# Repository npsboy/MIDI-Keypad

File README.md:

# MIDI Keypad — 8-bit edition

- **Sliders removed.** The encoder and the 3 Choc switches now share one top row, which frees a band above the keys.
- **A 5mm addressable RGB LED above each of the 7 touch keys.** They chain after the tutorial's 3 NeoPixels, so they use **no extra pins**.
- **A passive buzzer** (5V, 2048 Hz, 8 mm pin spacing), driven by a BC547 with a flyback diode.
- **Retro / chiptune pixel-art silkscreen** on both sides.

The finished project is in this folder (`MIDI-Keypad.kicad_pro`). Final checks: **ERC 0 errors / 0 warnings, DRC 0 violations / 0 unconnected** (`ERC_report.txt`, `DRC_report.txt`). Files to order with are in `production/`.

## Folder layout
- `MIDI-Keypad.*`: the finished KiCad project
- `production/`: Gerber zip for JLCPCB, BOM, positions, netlist
- `libraries/`: everything the project needs, linked relative to the project (no global KiCad setup required):
  - the tutorial's Hack Club symbols and footprints
  - this project's own symbol and footprints (`MIDI-Keypad.*`)
  - the 3D models

## Pin map (for the firmware)
| ESP32-S3-Zero pin | Function |
|---|---|
| GP2 | LED data: all 10 addressable LEDs, one chain |
| GP3 | Buzzer (PWM / tone). HIGH turns the transistor on |
| GP4 / GP5 / GP6 | SW3 / SW2 / SW1 (to GND, use internal pull-ups) |
| GP7 ... GP13 | TOUCH7 ... TOUCH1 (key 7 ... key 1, left to right is key 1 to 7) |
| TX (GPIO43) / RX (GPIO44) | Encoder A / B (to GND, use internal pull-ups) |
| GP1 | spare |

**LED chain order:**

| Index | LED | Position |
|---|---|---|
| 0 | D1 | under SW3 |
| 1 | D2 | under SW2 |
| 2 | D3 | under SW1 |
| 3-9 | D4-D10 | above keys 1-7 |

## Parts
| Ref | Qty | Part | Notes |
|---|---|---|---|
| U1 | 1 | Waveshare ESP32-S3-Zero | |
| SW1-SW3 | 3 | Kailh Choc low-profile switch | + Choc keycaps |
| SW4 | 1 | EC11 rotary encoder (vertical) | + a knob |
| D1-D3 | 3 | SK6812MINI-E | reverse-mounted on the back, shine through the board |
| D4-D10 | 7 | XINGLIGHT XL-504RGBC-WS2812B, 5mm | the Amazon.in listing B0HN43Y547. Pin 1 (DIN) is at the **flat side** |
| BZ1 | 1 | passive buzzer 5V 30mA 2048 Hz, 8 mm pitch | the Amazon.in listing B07M6517H8. "+" pin goes to the square pad |
| Q1 | 1 | BC547 (TO-92) | match the flat face to the flat side of the silkscreen outline. Collector goes on the square pad |
| R1 | 1 | 1 kΩ 1/4 W resistor | mounted standing up |
| D11 | 1 | 1N4148 | mounted standing up, **cathode (band) to the square pad** |

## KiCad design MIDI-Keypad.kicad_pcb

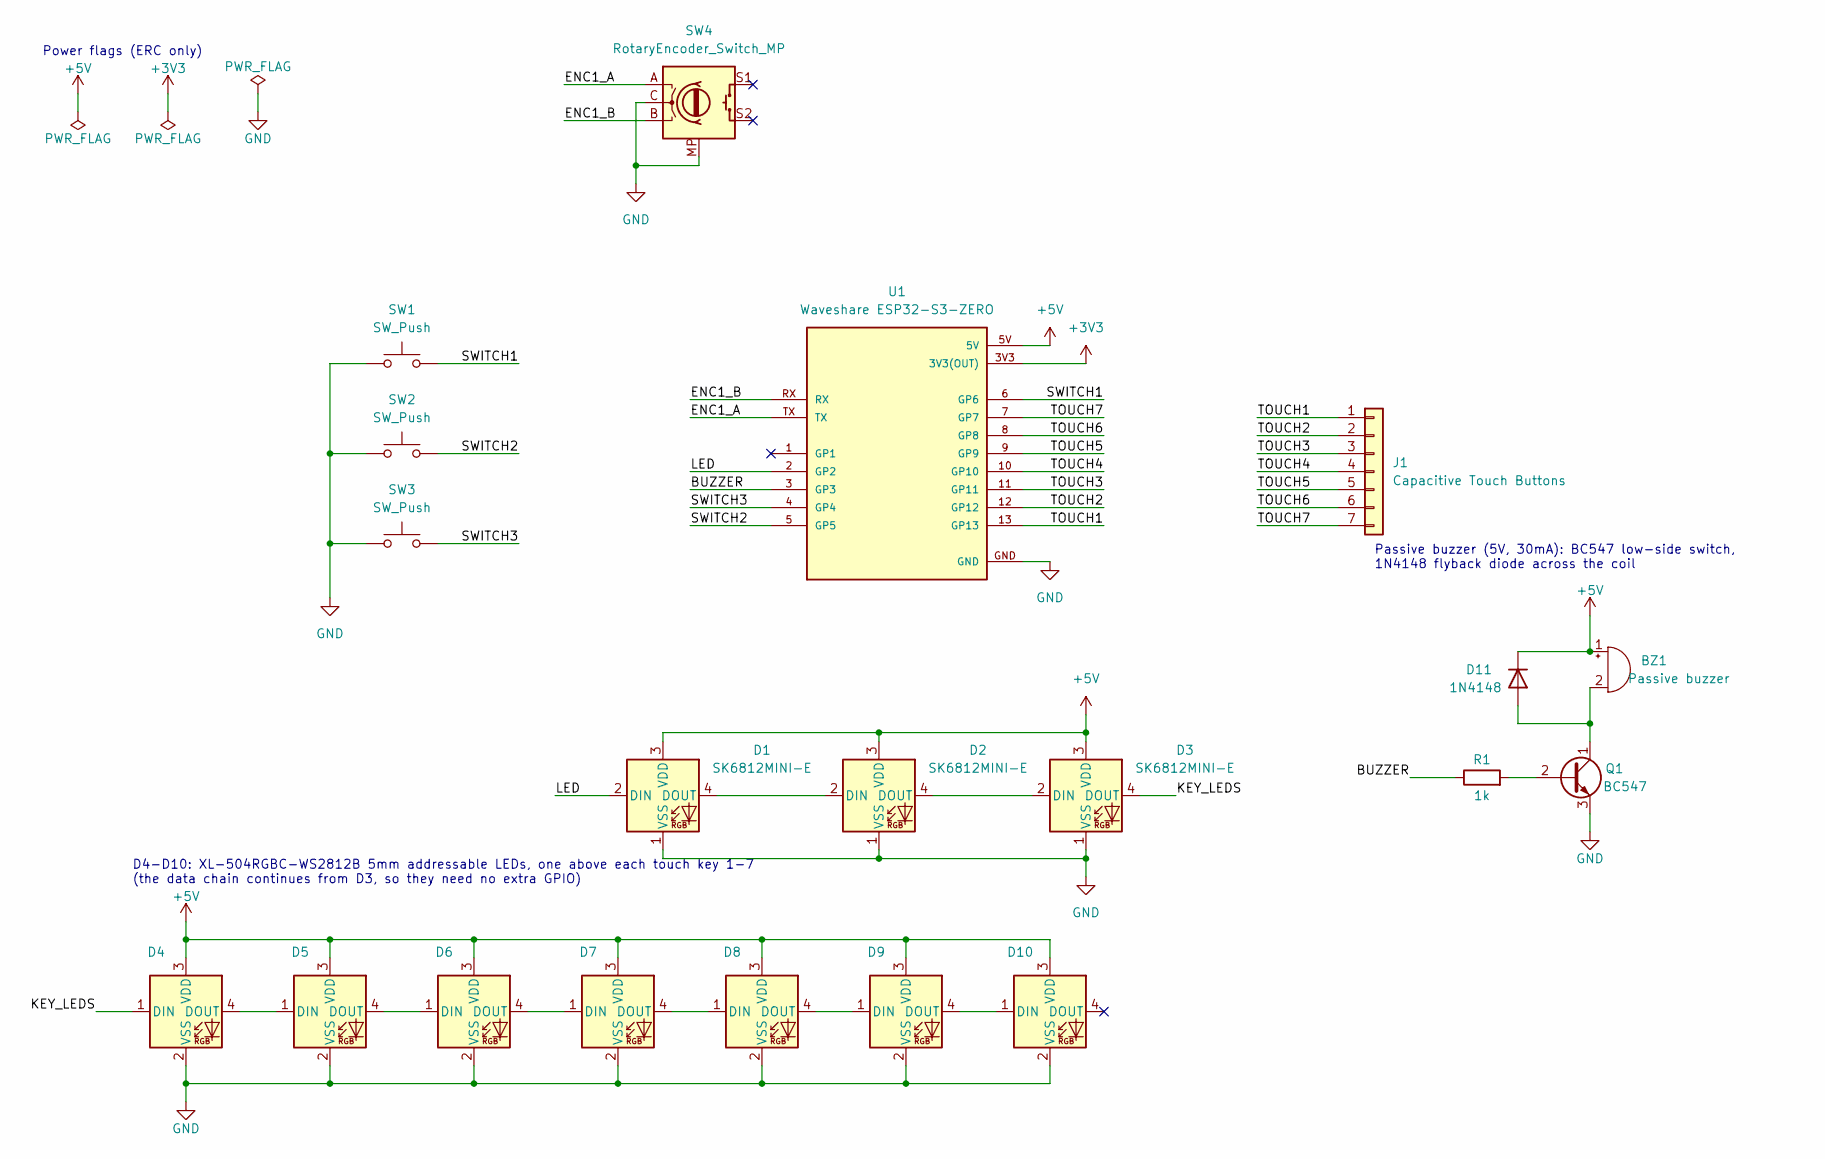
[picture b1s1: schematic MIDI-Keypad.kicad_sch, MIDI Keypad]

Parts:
BZ1: Passive buzzer; Buzzer_12x9.5_P8.0mm
D1, D2, D3: SK6812MINI-E; LED_SK6812MINI-E_3.2x2.8mm_P1.5mm_ReverseMount
D4, D5, D6, D7, D8, D9, D10: XL-504RGBC-WS2812B; LED_D5.0mm-4_XL-504RGBC-WS2812B
D11: 1N4148; D_DO-35_SOD27_P2.54mm_Vertical_CathodeUp
J1: Capacitive Touch Buttons; Capacitive Keys
Q1: BC547; TO-92_Inline
R1: 1k; R_Axial_DIN0207_L6.3mm_D2.5mm_P2.54mm_Vertical
SW1, SW2, SW3: SW_Push; Kailh Choc Low-Profile Switches
SW4: RotaryEncoder_Switch_MP; RotaryEncoder_Alps_EC11E-Switch_Vertical_H20mm
U1: Waveshare ESP32-S3-ZERO; Waveshare ESP32-S3-Zero; PARTREV NA

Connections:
+3V3: U1.3V3 (3V3(OUT))
+5V: BZ1.1 (+), D1.3 (VDD), D2.3 (VDD), D3.3 (VDD), D4.3 (VDD), D5.3 (VDD), D6.3 (VDD), D7.3 (VDD), D8.3 (VDD), D9.3 (VDD), D10.3 (VDD), D11.1 (K), U1.5V
/BUZZER: R1.1, U1.3 (GP3)
/ENC1_A: SW4.A, U1.TX
/ENC1_B: SW4.B, U1.RX
/KEY_LEDS: D3.4 (DOUT), D4.1 (DIN)
/LED: D1.2 (DIN), U1.2 (GP2)
/SWITCH1: SW1.2, U1.6 (GP6)
/SWITCH2: SW2.2, U1.5 (GP5)
/SWITCH3: SW3.2, U1.4 (GP4)
/TOUCH1: J1.1, U1.13 (GP13)
/TOUCH2: J1.2, U1.12 (GP12)
/TOUCH3: J1.3, U1.11 (GP11)
/TOUCH4: J1.4, U1.10 (GP10)
/TOUCH5: J1.5, U1.9 (GP9)
/TOUCH6: J1.6, U1.8 (GP8)
/TOUCH7: J1.7, U1.7 (GP7)
GND: D1.1 (VSS), D2.1 (VSS), D3.1 (VSS), D4.2 (VSS), D5.2 (VSS), D6.2 (VSS), D7.2 (VSS), D8.2 (VSS), D9.2 (VSS), D10.2 (VSS), Q1.3 (E), SW1.1, SW2.1, SW3.1, SW4.C, SW4.MP, U1.GND
unnamed: BZ1.2 (-), D11.2 (A), Q1.1 (C)
unnamed: D1.4 (DOUT), D2.2 (DIN)
unnamed: D2.4 (DOUT), D3.2 (DIN)
unnamed: D4.4 (DOUT), D5.1 (DIN)
unnamed: D5.4 (DOUT), D6.1 (DIN)
unnamed: D6.4 (DOUT), D7.1 (DIN)
unnamed: D7.4 (DOUT), D8.1 (DIN)
unnamed: D8.4 (DOUT), D9.1 (DIN)
unnamed: D9.4 (DOUT), D10.1 (DIN)
unnamed: Q1.2 (B), R1.2

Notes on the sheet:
Power flags (ERC only)
D4-D10: XL-504RGBC-WS2812B 5mm addressable LEDs, one above each touch key 1-7 (the data chain continues from D3, so they need no extra GPIO)
Passive buzzer (5V, 30mA): BC547 low-side switch, 1N4148 flyback diode across the coil

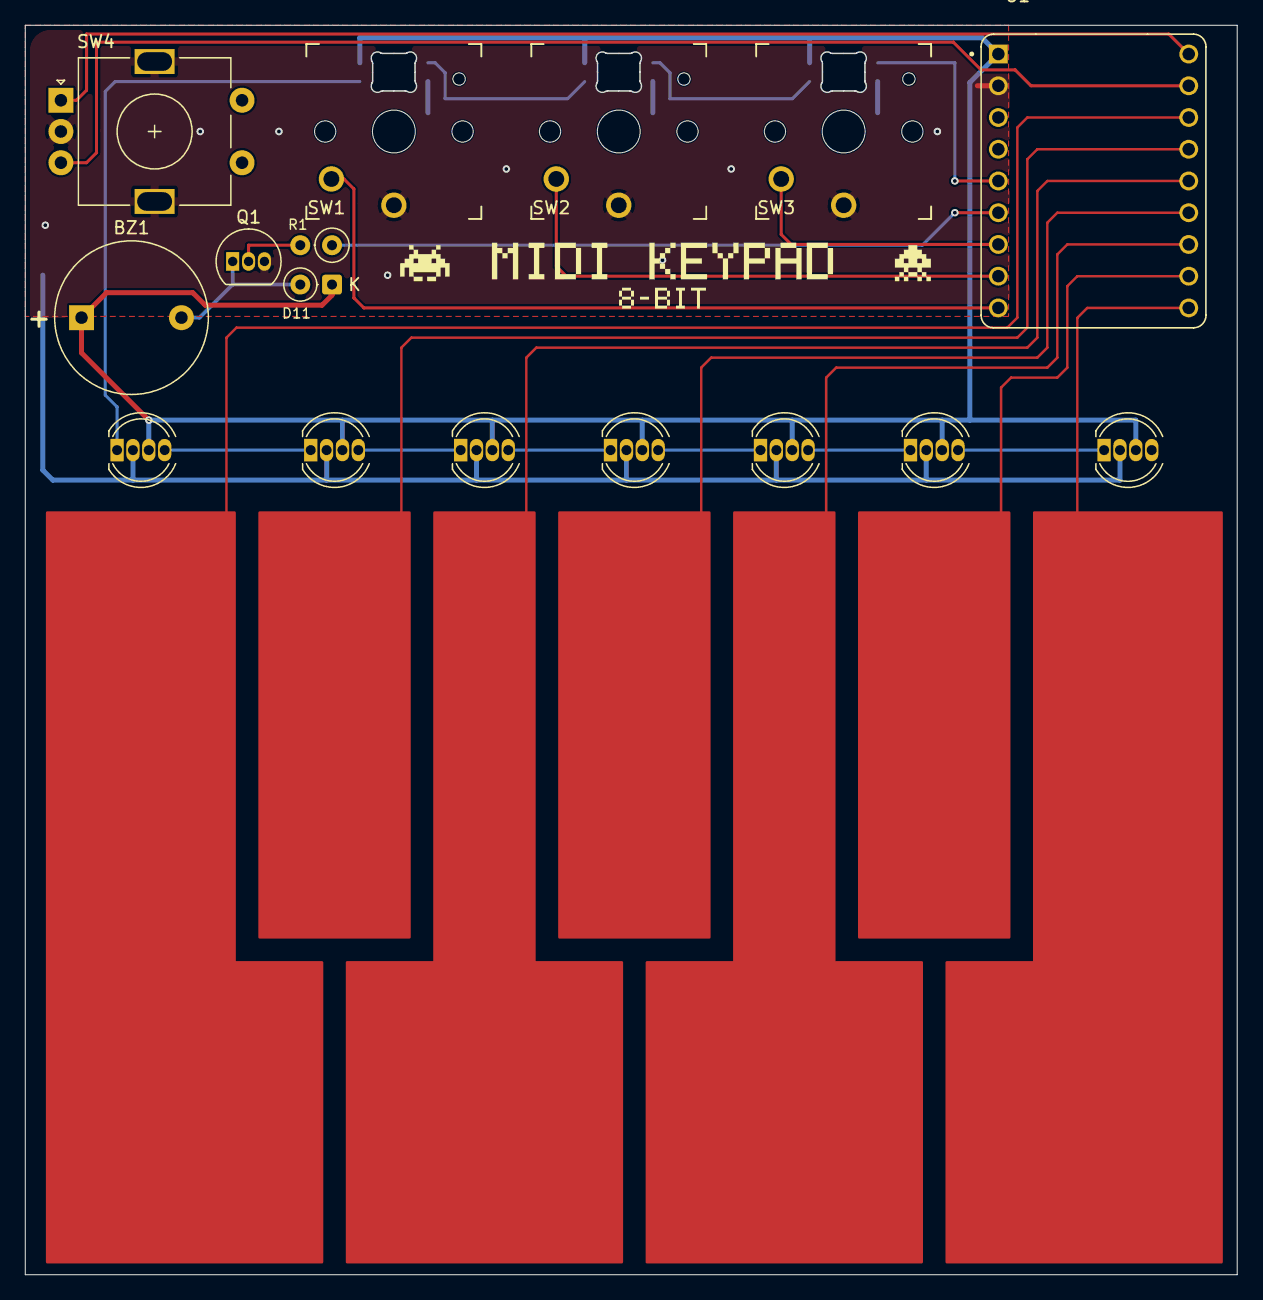
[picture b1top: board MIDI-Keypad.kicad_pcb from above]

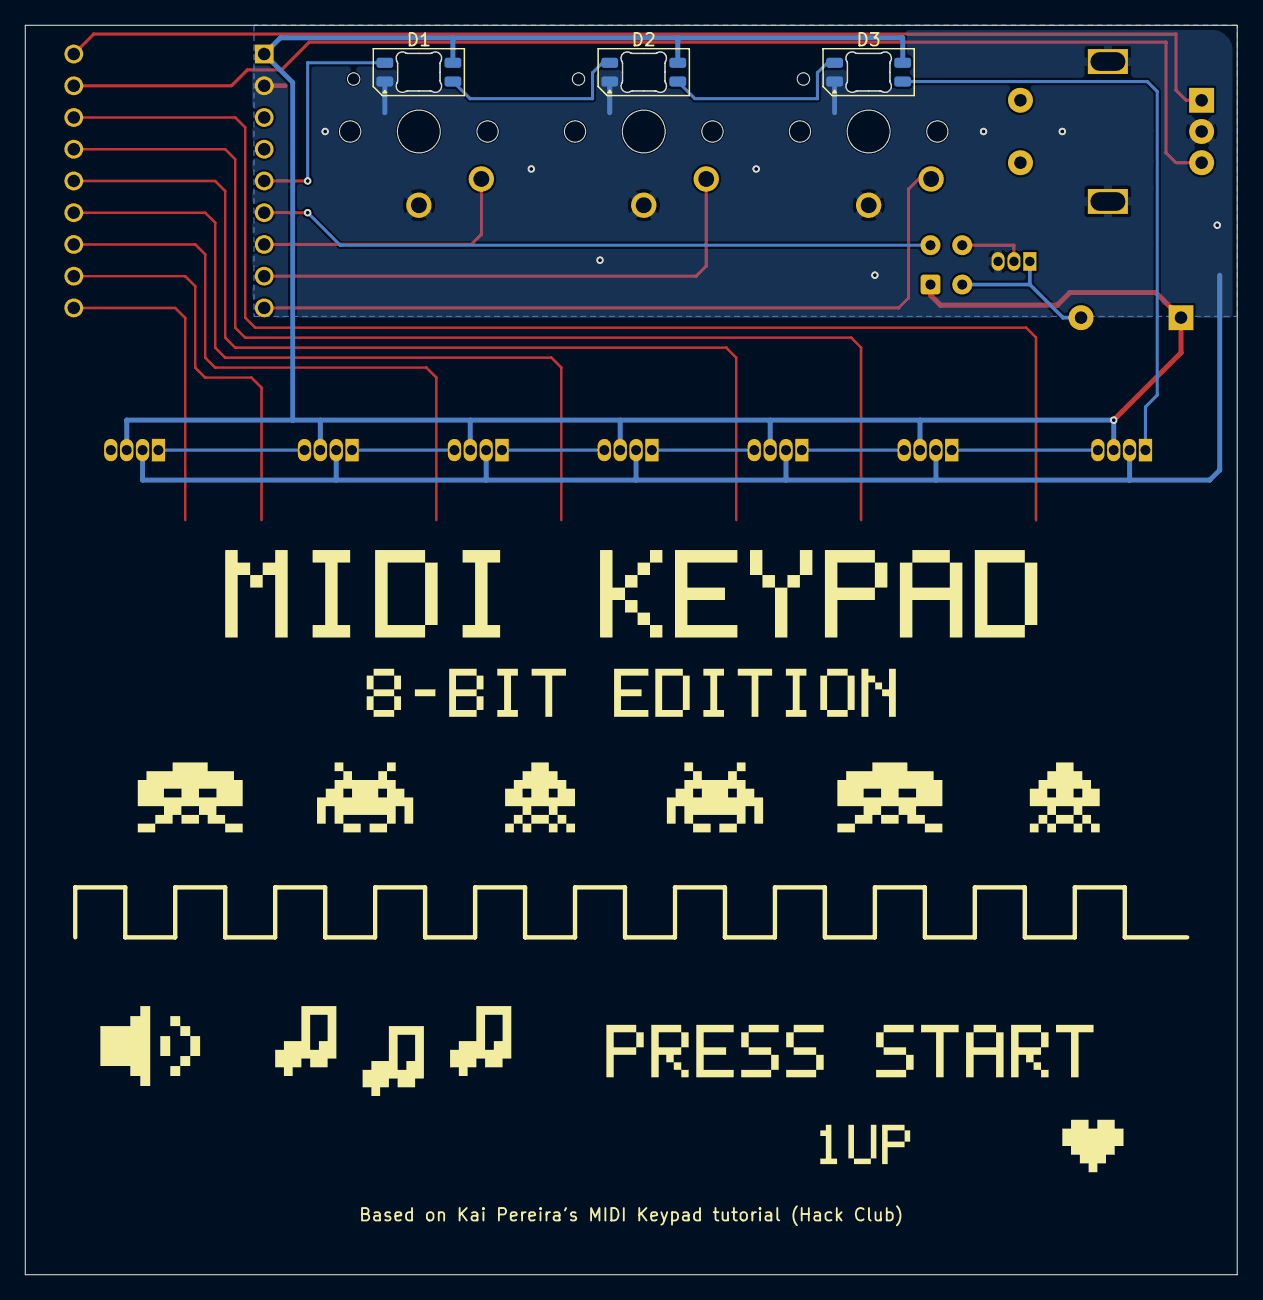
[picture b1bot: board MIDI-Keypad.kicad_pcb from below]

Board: 2 copper layers, 97.0 x 100.0 mm, 20 parts (3 on the bottom side), 27 nets.

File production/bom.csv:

Designator,Footprint,Quantity,Value,LCSC Part #
BZ1,Buzzer_12x9.5_P8.0mm,1,Passive buzzer,
D1-D3,LED_SK6812MINI-E_3.2x2.8mm_P1.5mm_ReverseMount,3,SK6812MINI-E,
D4-D10,LED_D5.0mm-4_XL-504RGBC-WS2812B,7,XL-504RGBC-WS2812B,
D11,D_DO-35_SOD27_P2.54mm_Vertical_CathodeUp,1,1N4148,
J1,Capacitive Keys,1,Capacitive Touch Buttons,
Q1,TO-92_Inline,1,BC547,
R1,R_Axial_DIN0207_L6.3mm_D2.5mm_P2.54mm_Vertical,1,1k,
SW1-SW3,Kailh Choc Low-Profile Switches,3,SW_Push,
SW4,RotaryEncoder_Alps_EC11E-Switch_Vertical_H20mm,1,RotaryEncoder_Switch_MP,
U1,Waveshare ESP32-S3-Zero,1,Waveshare ESP32-S3-ZERO,
